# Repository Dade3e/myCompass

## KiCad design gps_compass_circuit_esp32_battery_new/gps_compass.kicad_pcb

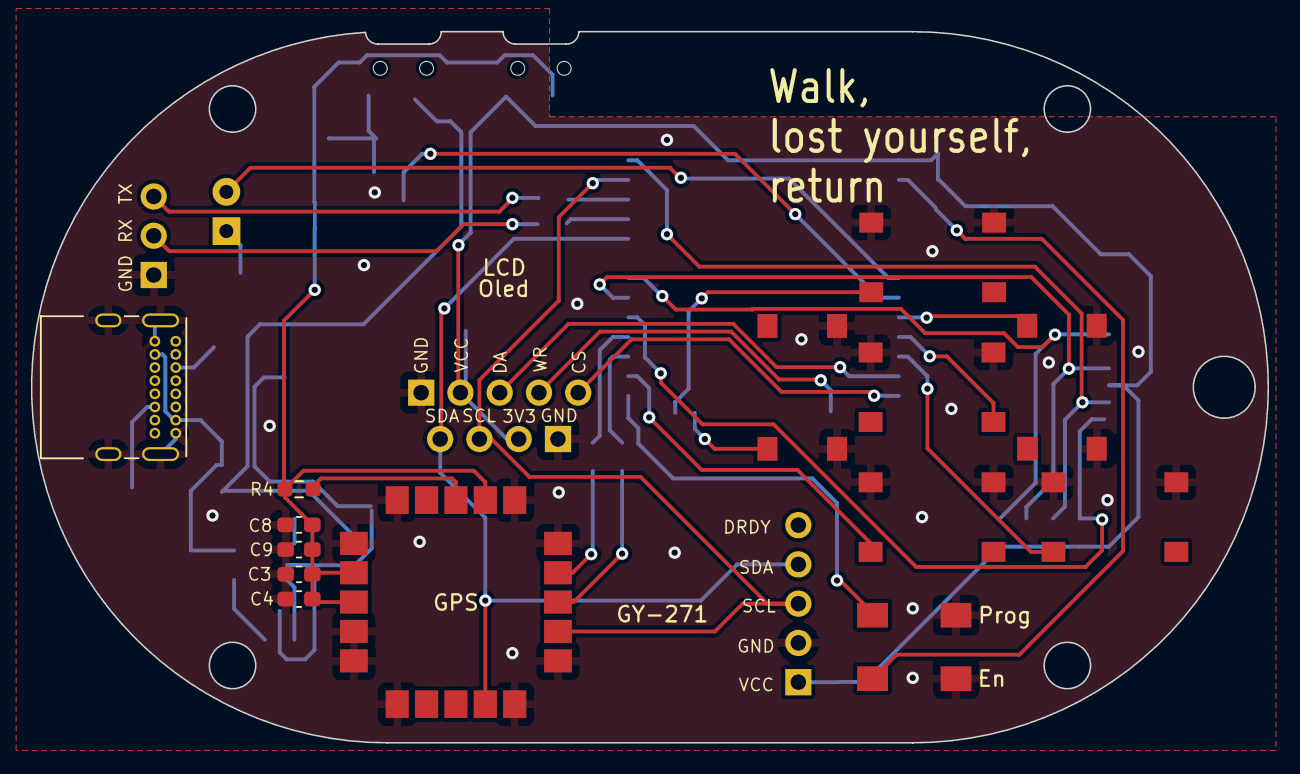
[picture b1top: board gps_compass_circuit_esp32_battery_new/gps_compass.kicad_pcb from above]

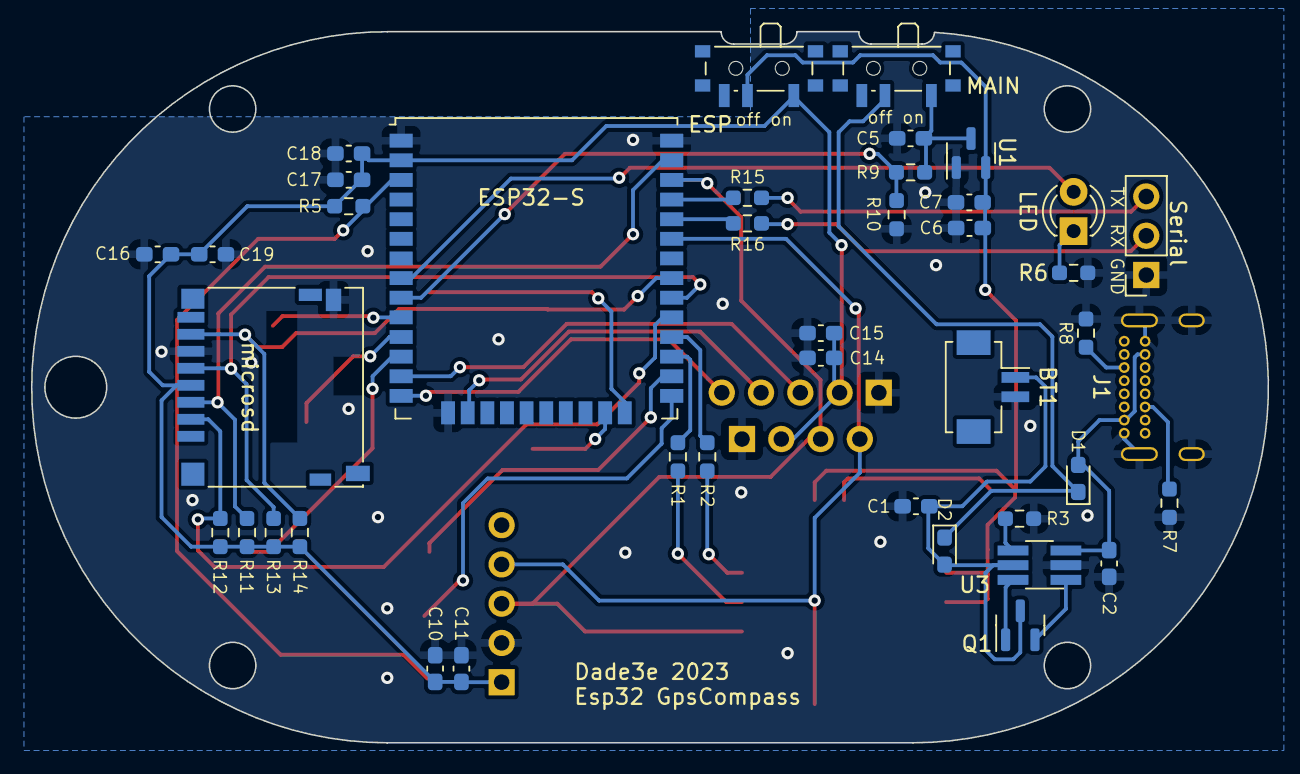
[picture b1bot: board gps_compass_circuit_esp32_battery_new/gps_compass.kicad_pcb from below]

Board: 2 copper layers, 80.0 x 46.0 mm, 58 parts (40 on the bottom side), 41 nets.

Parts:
BT1: Battery_Cell; Hirose_DF13C_CL535-0402-2-51_1x02-1MP_P1.25mm_Vertical
C1: 10uF; C_0603_1608Metric_Pad1.08x0.95mm_HandSolder
C2, C5, C7, C9, C11, C15, C18, C19: 1uF; C_0603_1608Metric_Pad1.08x0.95mm_HandSolder
C3, C4, C6, C8, C10, C14, C16, C17: 0,1uF; C_0603_1608Metric_Pad1.08x0.95mm_HandSolder
D1, D2: D; D_0603_1608Metric_Pad1.05x0.95mm_HandSolder
ESP: SW_SPDT; SW_SPDT_PCM12
ESP32-S: ESP32-WROOM-32U
En: SW_SPST; SW_SPST_EVQPE1
GPS: SAM-M8Q; ublox_SAM-M8Q
GY-271: Conn_01x05_Socket; GY-271
J1: USB_C_Receptacle_PowerOnly_6P; USB_C_Receptacle_GCT_USB4085
LCD: Conn_01x05_Socket; display_7_segm_4_digits
LED: LED; LED_D3.0mm
MAIN: SW_SPDT; SW_SPDT_PCM12
Oled: Conn_01x04_Socket; Display_i2c_128x64
Prog: SW_SPST; SW_SPST_EVQPE1
Q1: MMBTA92; SOT-23
R1, R2, R15, R16: 100R; R_0603_1608Metric_Pad0.98x0.95mm_HandSolder
R3: 5K; R_0603_1608Metric_Pad0.98x0.95mm_HandSolder
R4: 3,3K; R_0603_1608Metric_Pad0.98x0.95mm_HandSolder
R5, R11: 10K; R_0603_1608Metric_Pad0.98x0.95mm_HandSolder
R6: R; R_0603_1608Metric_Pad0.98x0.95mm_HandSolder
R7, R8: 5K1; R_0603_1608Metric_Pad0.98x0.95mm_HandSolder
R9: 27K; R_0603_1608Metric_Pad0.98x0.95mm_HandSolder
R10: 100K; R_0603_1608Metric_Pad0.98x0.95mm_HandSolder
R12, R13, R14: 47K; R_0603_1608Metric_Pad0.98x0.95mm_HandSolder
SWa1: SW_SPST; SW_Push_1P1T_NO_6x6mm_H9.5mm
SWb1: SW_SPST; SW_Push_1P1T_NO_6x6mm_H9.5mm
SWdown1: SW_SPST; SW_Push_1P1T_NO_6x6mm_H9.5mm
SWleft1: SW_SPST; SW_Push_1P1T_NO_6x6mm_H9.5mm
SWright1: SW_SPST; SW_Push_1P1T_NO_6x6mm_H9.5mm
SWup1: SW_SPST; SW_Push_1P1T_NO_6x6mm_H9.5mm
Serial: Conn_01x03_Socket; PinSocket_1x03_P2.54mm_Vertical
U1: MCP1700x-330xxTT; SOT-23
U3: LTC4054ES5-4.2; TSOT-23-6_HandSoldering
microsd: Micro_SD_Card; microSD_HC_Hirose_DM3D-SF

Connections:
+3V3: C3.1, C4.1, C6.1, C7.1, C8.1, C9.1, ESP.2 (B), GPS.2 (VCC_IO), GPS.3 (V_BCKP), GPS.17 (VCC), R4.2, U1.2 (VO)
+BATT: C5.1, MAIN.1 (A), R9.1, U1.3 (VI)
B1: ESP32-S.24 (IO2), SWup1.1 (A)
B2: ESP32-S.26 (IO4), SWdown1.1 (A)
B3: ESP32-S.23 (IO15), SWleft1.1 (A)
B4: ESP32-S.10 (IO25), SWright1.1 (A)
B5: ESP32-S.11 (IO26), SWa1.1 (A)
B6: ESP32-S.12 (IO27), SWb1.1 (A)
CLK: ESP32-S.30 (IO18), R13.2, microsd.5 (CLK)
CS: ESP32-S.29 (IO5), R12.2, microsd.2 (DAT3/CD)
GND: BT1.2 (-), C1.2, C2.2, C3.2, C4.2, C5.2, C6.2, C7.2, C8.2, C9.2, C10.1, C11.1, C14.1, C15.1, C16.2, C17.2, C18.2, C19.2, ESP32-S.1 (GND), ESP32-S.15 (GND), ESP32-S.38 (GND), En.1 (A), GPS.1 (GND), GPS.4 (GND), GPS.5 (GND), GPS.6 (GND), GPS.10 (GND), GPS.11 (GND), GPS.15 (GND), GPS.16 (GND), GPS.20 (GND), GY-271.2, J1.A12 (GND), J1.B12 (GND), J1.S1 (SHIELD), LCD.1, Oled.1, Prog.2 (B), R3.2, R6.2, R7.2, R8.2, R10.2, SWa1.2 (B), SWb1.2 (B), SWdown1.2 (B), SWleft1.2 (B), SWright1.2 (B), SWup1.2 (B), Serial.1, U1.1 (GND), U3.2 (GND), microsd.6 (VSS), microsd.9 (SHIELD)
MISO: ESP32-S.31 (IO19), R14.2, microsd.7 (DAT0)
MOSI: ESP32-S.37 (IO23), R11.2, microsd.3 (CMD)
unnamed: BT1.1 (+), C1.1, D2.2 (A), Q1.3 (C), U3.5 (BATT)
unnamed: C2.1, D1.2 (A), J1.A9 (VBUS), J1.B9 (VBUS), U3.3 (VCC)
unnamed: D1.1 (K), D2.1 (K), MAIN.2 (B)
unnamed: ESP32-S.8 (IO32), LED.2 (A)
unnamed: LED.1 (K), R6.1
unnamed: ESP32-S.3 (EN), En.2 (B), R5.2
unnamed: ESP32-S.25 (IO0), Prog.1 (A)
unnamed: ESP32-S.34 (RXD0/IO3), R16.1
unnamed: ESP32-S.35 (TXD0/IO1), R15.1
unnamed: GPS.14 (RXD), R2.2
unnamed: GPS.13 (TXD), R1.2
unnamed: GPS.18 (~RESET), R4.1
unnamed: J1.A5 (CC1), R8.1
unnamed: J1.B5 (CC2), R7.1
unnamed: Q1.1 (B), U3.6 (DRIVE)
unnamed: Q1.2 (E), U3.1 (Isense)
unnamed: R16.2, Serial.2
unnamed: R15.2, Serial.3
unnamed: R3.1, U3.4 (Prog)
RX2: ESP32-S.27 (IO16), R1.1
SCL: ESP32-S.36 (IO22), GPS.12 (SCL), GY-271.3, Oled.3
SDA: ESP32-S.33 (IO21), GPS.9 (SDA), GY-271.4, Oled.4
TX2: ESP32-S.28 (IO17), R2.1
VCC: C10.2, C11.2, C14.2, C15.2, C16.1, C17.1, C18.1, C19.1, ESP.1 (A), ESP32-S.2 (VDD), GY-271.1, LCD.2, Oled.2, R5.1, R11.1, R12.1, R13.1, R14.1, microsd.4 (VDD)
battery_level: ESP32-S.9 (IO33), R9.2, R10.1
lcd_cs: ESP32-S.14 (IO12), LCD.5
lcd_data: ESP32-S.13 (IO14), LCD.3
lcd_wr: ESP32-S.16 (IO13), LCD.4

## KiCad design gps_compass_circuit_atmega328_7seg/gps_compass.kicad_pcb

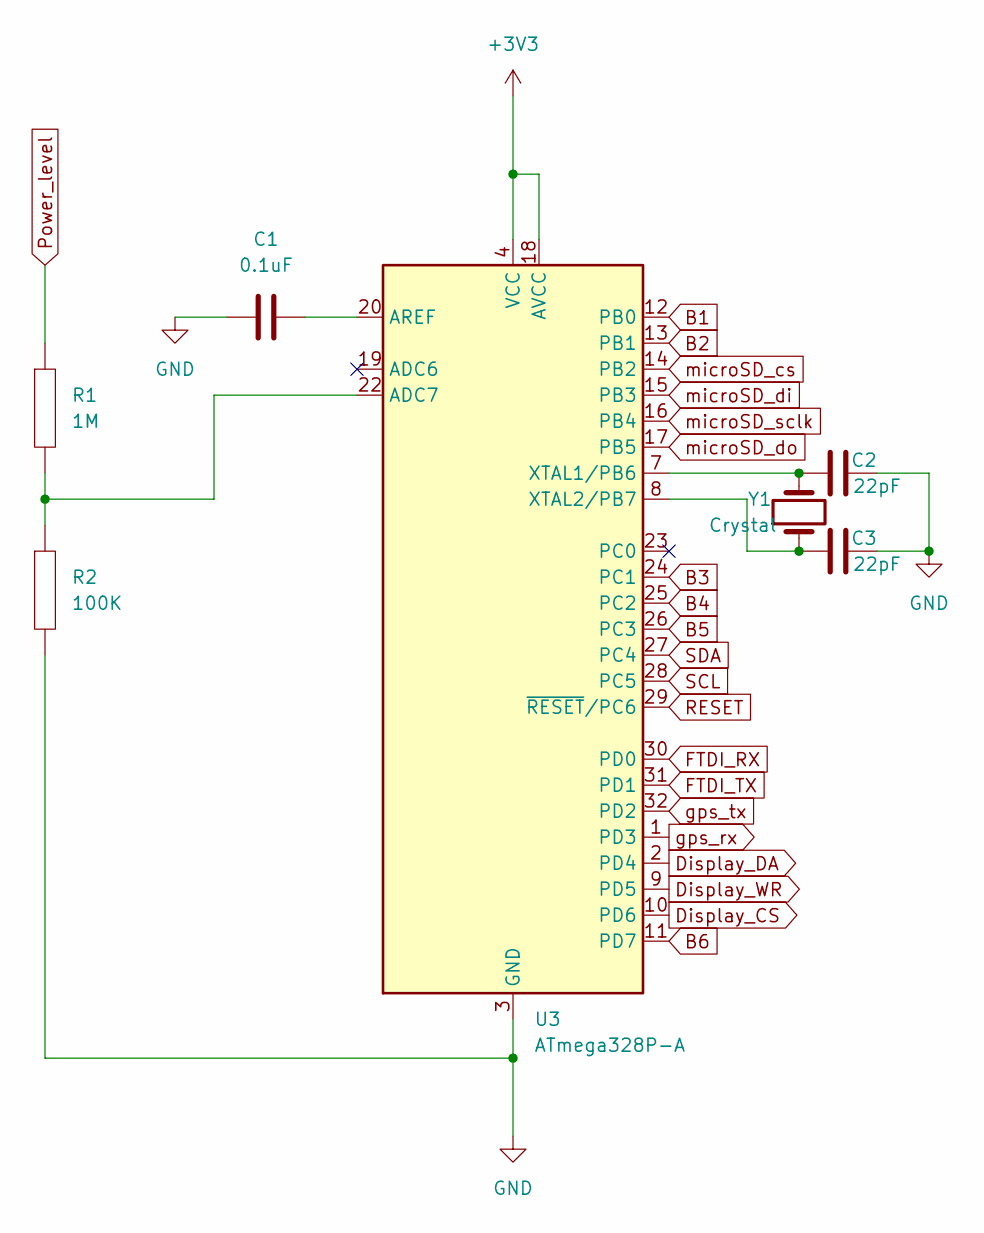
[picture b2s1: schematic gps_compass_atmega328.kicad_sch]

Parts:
C1: 0.1uF; C_0603_1608Metric
C2, C3: 22pF; C_0603_1608Metric
R1: 1M; C_0603_1608Metric
R2: 100K; C_0603_1608Metric
U3: ATmega328P-A; TQFP-32_7x7mm_P0.8mm
Y1: Crystal; Resonator-2Pin_W10.0mm_H5.0mm

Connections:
+3V3: U3.4 (VCC), U3.6 (VCC), U3.18 (AVCC); also elsewhere on the board
B1: U3.12 (PB0); also elsewhere on the board
B2: U3.13 (PB1); also elsewhere on the board
B3: U3.24 (PC1); also elsewhere on the board
B4: U3.25 (PC2); also elsewhere on the board
B5: U3.26 (PC3); also elsewhere on the board
B6: U3.11 (PD7); also elsewhere on the board
Display_CS: U3.10 (PD6); also elsewhere on the board
Display_DA: U3.2 (PD4); also elsewhere on the board
Display_WR: U3.9 (PD5); also elsewhere on the board
FTDI_RX: U3.30 (PD0); also elsewhere on the board
FTDI_TX: U3.31 (PD1); also elsewhere on the board
GND: C1.1, C2.2, C3.2, R2.2, U3.3 (GND), U3.5 (GND), U3.21 (GND); also elsewhere on the board
unnamed: R1.2, R2.1, U3.22 (ADC7)
unnamed: C1.2, U3.20 (AREF)
unnamed: C2.1, U3.7 (XTAL1/PB6), Y1.2
unnamed: C3.1, U3.8 (XTAL2/PB7), Y1.1
Power_level: R1.1; also elsewhere on the board
RESET: U3.29 (~RESET/PC6); also elsewhere on the board
SCL: U3.28 (PC5); also elsewhere on the board
SDA: U3.27 (PC4); also elsewhere on the board
gps_rx: U3.1 (PD3); also elsewhere on the board
gps_tx: U3.32 (PD2); also elsewhere on the board
microSD_cs: U3.14 (PB2); also elsewhere on the board
microSD_di: U3.15 (PB3); also elsewhere on the board
microSD_do: U3.17 (PB5); also elsewhere on the board
microSD_sclk: U3.16 (PB4); also elsewhere on the board

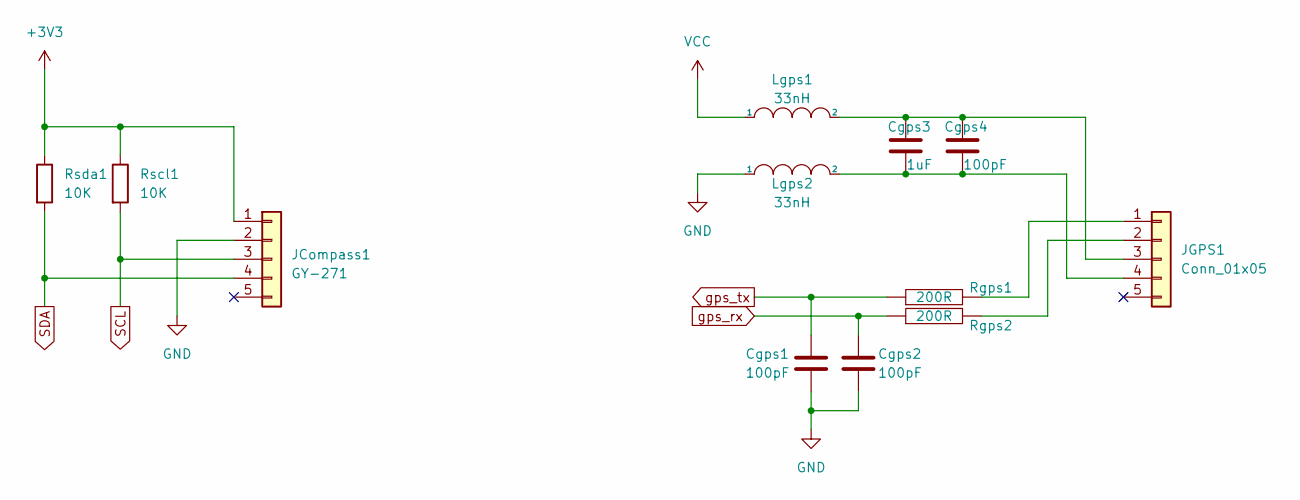
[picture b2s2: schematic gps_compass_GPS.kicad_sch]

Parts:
Cgps1, Cgps2, Cgps4: 100pF; C_0603_1608Metric
Cgps3: 1uF; C_0603_1608Metric
JCompass1: GY-271
JGPS1: Conn_01x05; PinSocket_1x05_P2.54mm_Vertical
Lgps1, Lgps2: 33nH; L_0603_1608Metric
Rgps1, Rgps2: 200R; R_0603_1608Metric
Rscl1: 10K; R_0603_1608Metric
Rsda1: 10K; R_0603_1608Metric

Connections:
+3V3: JCompass1.1, Rscl1.1, Rsda1.1; also elsewhere on the board
GND: Cgps1.2, Cgps2.2, JCompass1.2, Lgps2.1; also elsewhere on the board
unnamed: JGPS1.1, Rgps1.2
unnamed: JGPS1.2, Rgps2.2
unnamed: Cgps3.1, Cgps4.1, JGPS1.3, Lgps1.2
unnamed: Cgps3.2, Cgps4.2, JGPS1.4, Lgps2.2
SCL: JCompass1.3, Rscl1.2; also elsewhere on the board
SDA: JCompass1.4, Rsda1.2; also elsewhere on the board
VCC: Lgps1.1; also elsewhere on the board
gps_rx: Cgps2.1, Rgps2.1; also elsewhere on the board
gps_tx: Cgps1.1, Rgps1.1; also elsewhere on the board

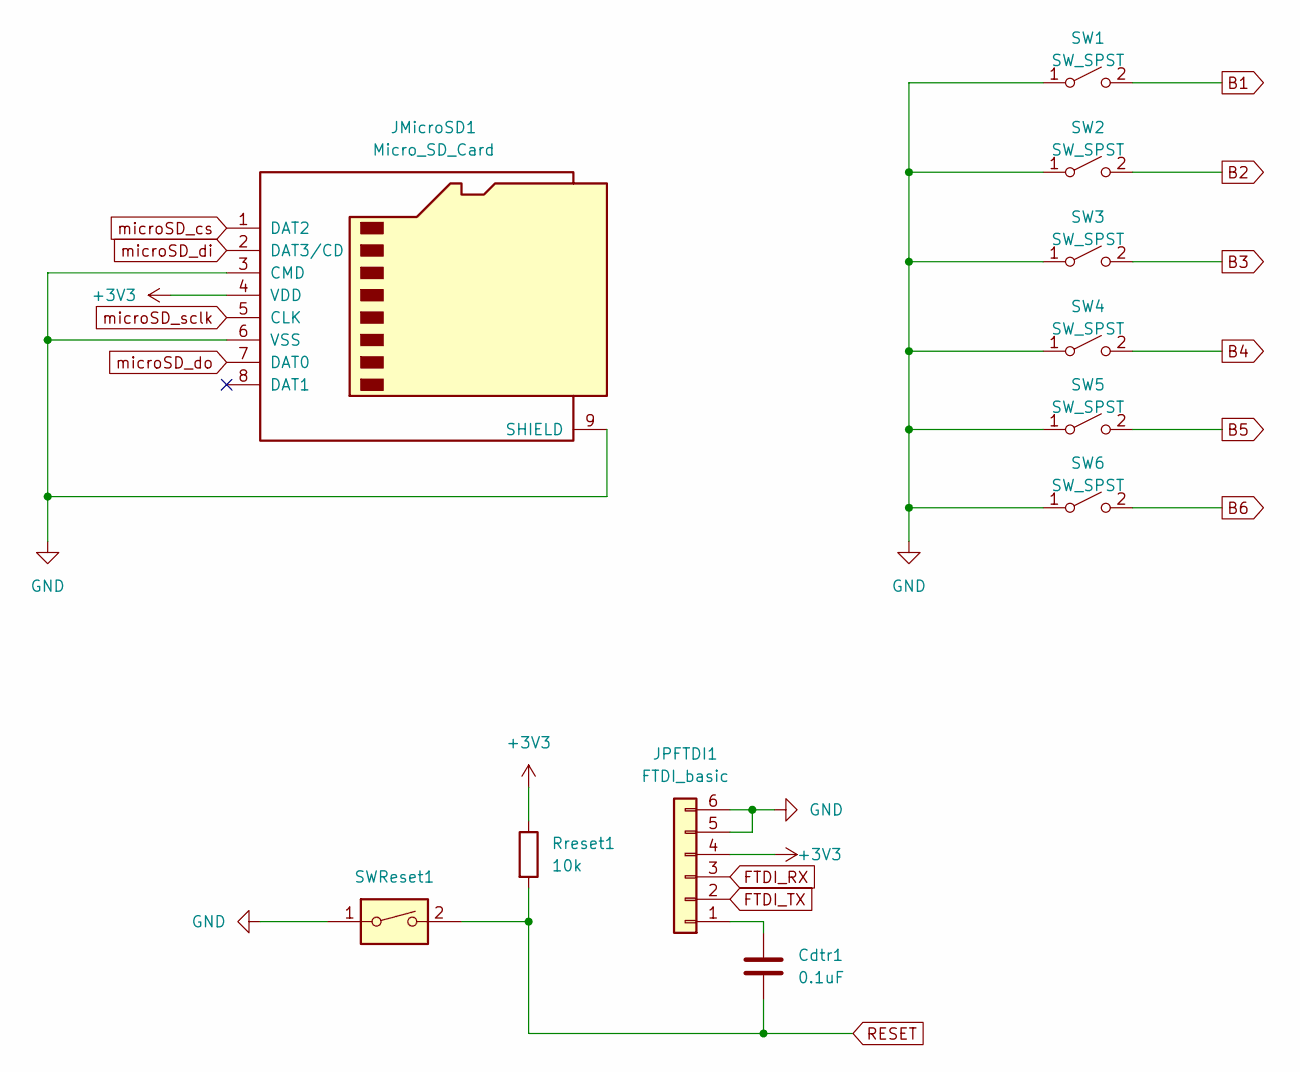
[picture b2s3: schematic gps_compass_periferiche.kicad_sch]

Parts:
Cdtr1: 0.1uF; R_0603_1608Metric
JMicroSD1: Micro_SD_Card; microSD_HC_Molex_47219-2001
JPFTDI1: FTDI_basic; PinSocket_1x06_P2.54mm_Horizontal
Rreset1: 10k; R_0603_1608Metric
SW1, SW2, SW3, SW4, SW5, SW6: SW_SPST; SW_PUSH_6mm
SWReset1: SW_Reset; SW_PUSH_6mm

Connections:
+3V3: JMicroSD1.4 (VDD), JPFTDI1.4, Rreset1.1; also elsewhere on the board
B1: SW1.2 (B); also elsewhere on the board
B2: SW2.2 (B); also elsewhere on the board
B3: SW3.2 (B); also elsewhere on the board
B4: SW4.2 (B); also elsewhere on the board
B5: SW5.2 (B); also elsewhere on the board
B6: SW6.2 (B); also elsewhere on the board
FTDI_RX: JPFTDI1.3; also elsewhere on the board
FTDI_TX: JPFTDI1.2; also elsewhere on the board
GND: JMicroSD1.3 (CMD), JMicroSD1.6 (VSS), JMicroSD1.9 (SHIELD), JPFTDI1.5, JPFTDI1.6, SW1.1 (A), SW2.1 (A), SW3.1 (A), SW4.1 (A), SW5.1 (A), SW6.1 (A), SWReset1.1; also elsewhere on the board
unnamed: Cdtr1.2, JPFTDI1.1
RESET: Cdtr1.1, Rreset1.2, SWReset1.2; also elsewhere on the board
microSD_cs: JMicroSD1.1 (DAT2); also elsewhere on the board
microSD_di: JMicroSD1.2 (DAT3/CD); also elsewhere on the board
microSD_do: JMicroSD1.7 (DAT0); also elsewhere on the board
microSD_sclk: JMicroSD1.5 (CLK); also elsewhere on the board

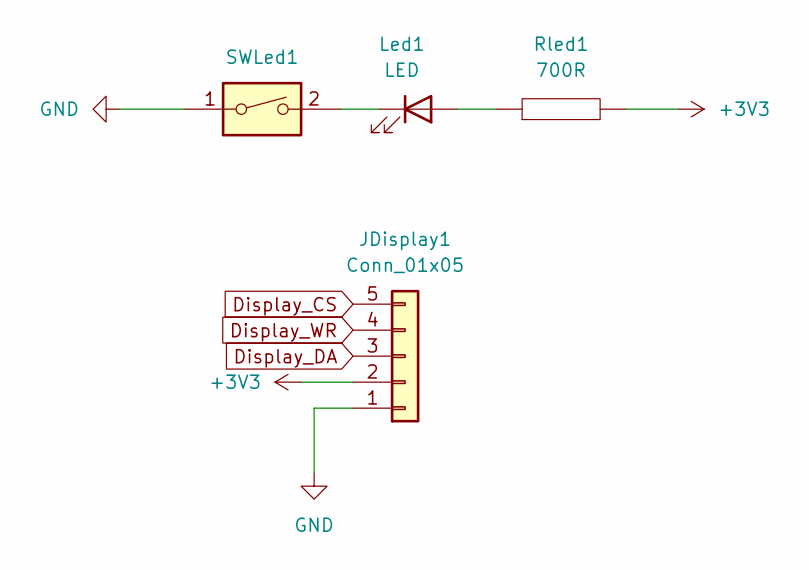
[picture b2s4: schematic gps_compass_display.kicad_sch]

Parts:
JDisplay1: Conn_01x05; display_7_segm_4_digits
Led1: LED; LED_D3.0mm
Rled1: 700R; R_0603_1608Metric
SWLed1: SW_Reset; SW_PUSH_6mm

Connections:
+3V3: JDisplay1.2, Rled1.2; also elsewhere on the board
Display_CS: JDisplay1.5; also elsewhere on the board
Display_DA: JDisplay1.3; also elsewhere on the board
Display_WR: JDisplay1.4; also elsewhere on the board
GND: JDisplay1.1, SWLed1.1; also elsewhere on the board
unnamed: Led1.2 (A), Rled1.1
unnamed: Led1.1 (K), SWLed1.2

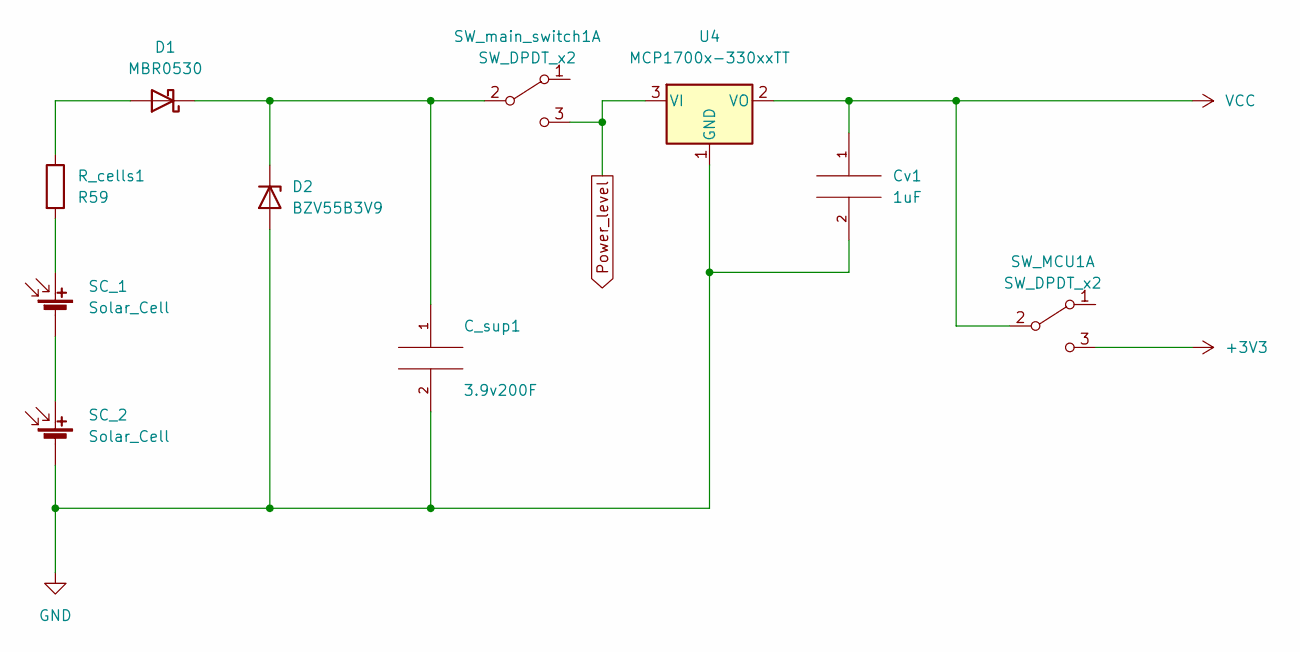
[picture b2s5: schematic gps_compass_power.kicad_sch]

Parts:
C_sup1: 3.9v200F; C_Rect_L9.0mm_W2.5mm_P7.50mm_MKT
Cv1: 1uF; C_0603_1608Metric
D1: MBR0530; D_SOD-123
D2: BZV55B3V9; D_A-405_P7.62mm_Horizontal
R_cells1: R59; R_0603_1608Metric
SC_1, SC_2: Solar_Cell; solar_panel
SW_MCU1: SW_DPDT_x2; PinSocket_1x03_P2.54mm_Vertical
SW_main_switch1: SW_DPDT_x2; PinSocket_1x03_P2.54mm_Vertical
U4: MCP1700x-330xxTT; SOT-23

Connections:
+3V3: SW_MCU1.3 (C); also elsewhere on the board
GND: C_sup1.2, Cv1.2, D2.2 (A), SC_2.2 (-), U4.1 (GND); also elsewhere on the board
unnamed: D1.2 (A), R_cells1.1
unnamed: C_sup1.1, D1.1 (K), D2.1 (K), SW_main_switch1.2 (B)
unnamed: R_cells1.2, SC_1.1 (+)
unnamed: SC_1.2 (-), SC_2.1 (+)
Power_level: SW_main_switch1.3 (C), U4.3 (VI); also elsewhere on the board
VCC: Cv1.1, SW_MCU1.2 (B), U4.2 (VO); also elsewhere on the board

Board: 2 copper layers, 44 parts (0 on the bottom side), 39 nets, no tracks yet.

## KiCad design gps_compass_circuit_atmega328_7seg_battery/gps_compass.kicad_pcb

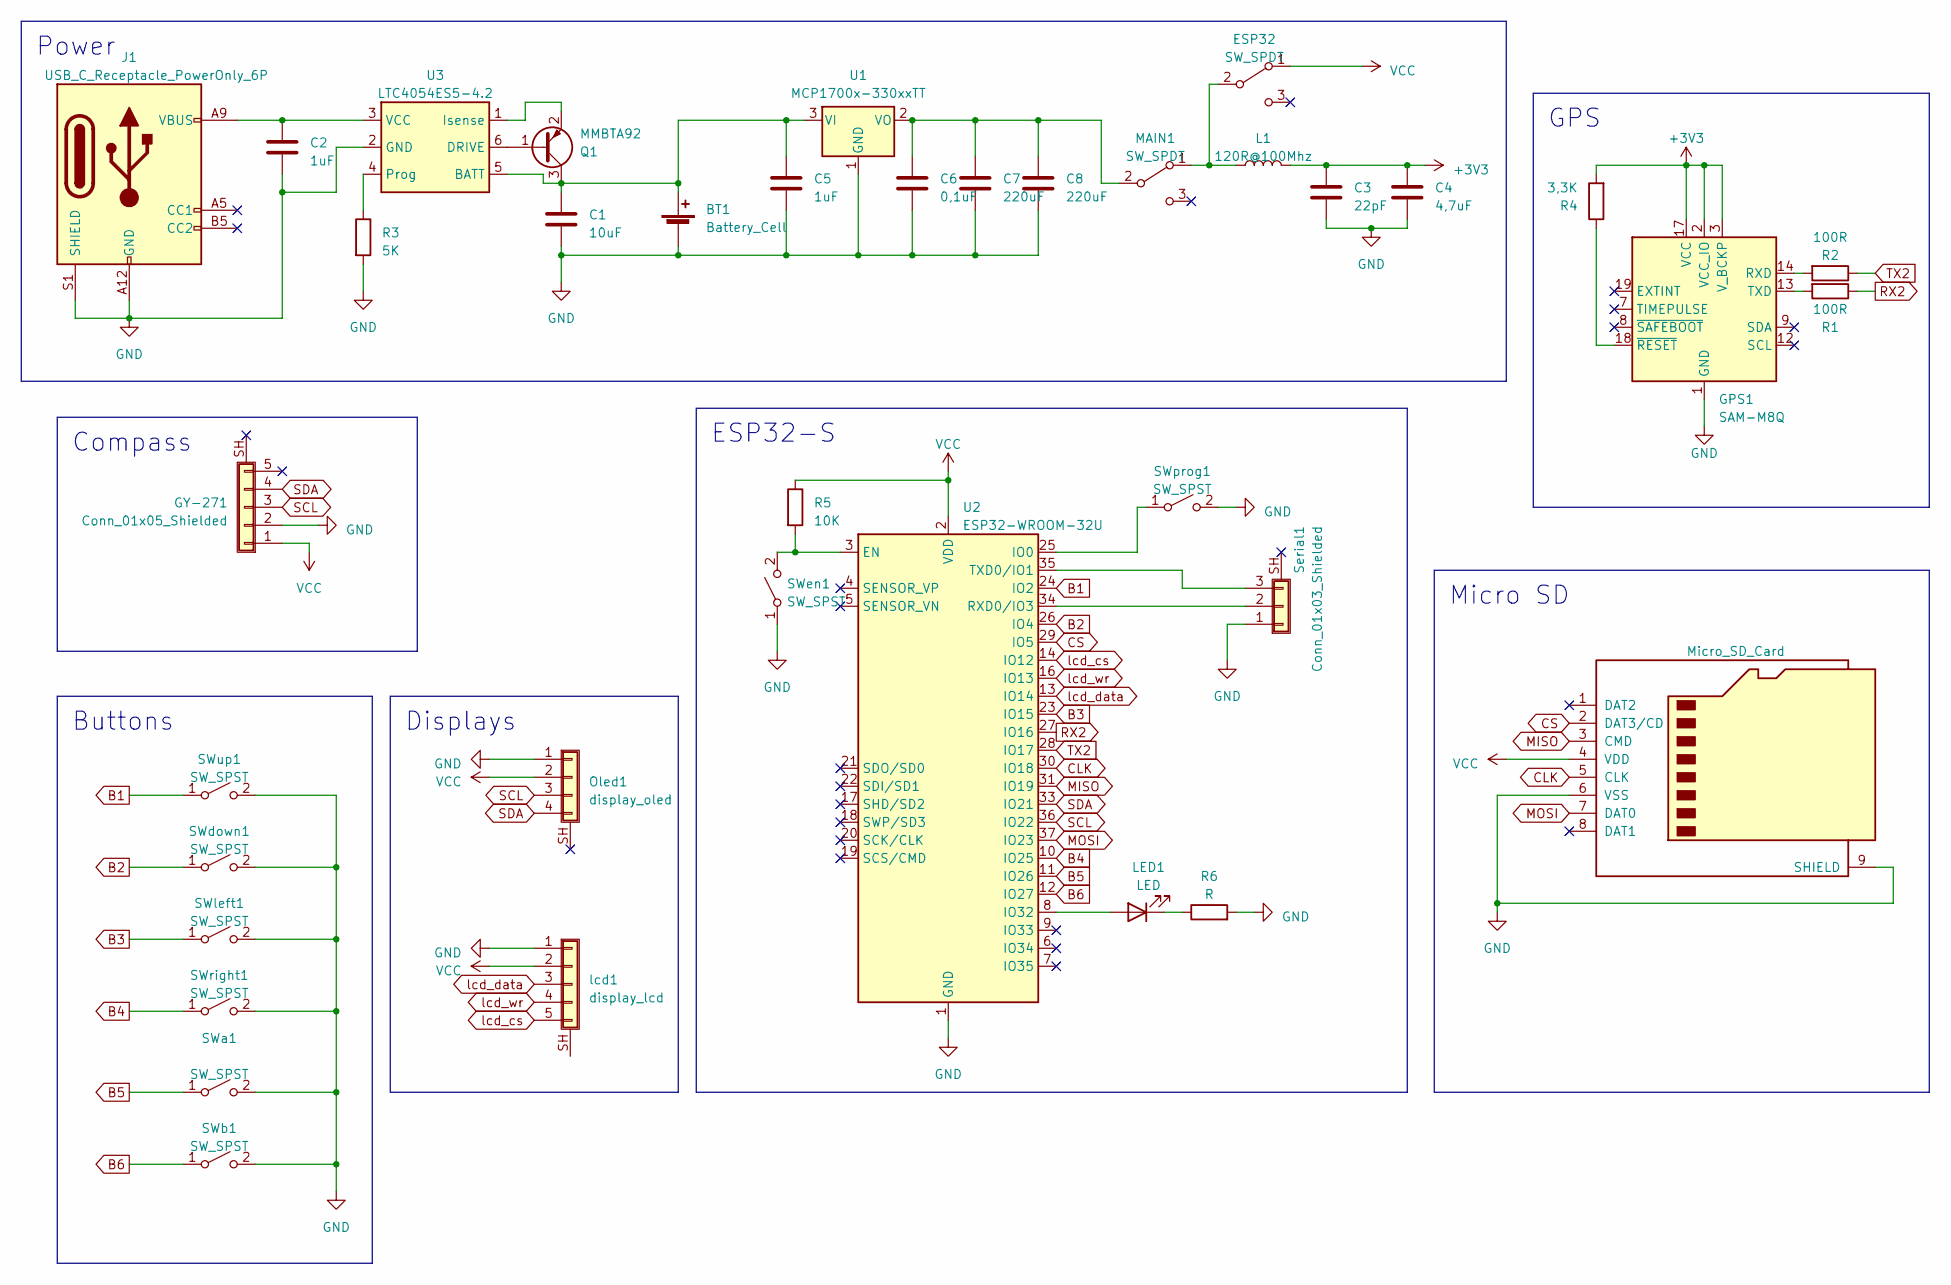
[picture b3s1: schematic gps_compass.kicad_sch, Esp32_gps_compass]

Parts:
BT1: Battery_Cell; Hirose_DF13C_CL535-0402-2-51_1x02-1MP_P1.25mm_Vertical
C1: 10uF; C_0805_2012Metric_Pad1.18x1.45mm_HandSolder
C2, C5: 1uF; C_0805_2012Metric_Pad1.18x1.45mm_HandSolder
C3: 22pF; C_0805_2012Metric_Pad1.18x1.45mm_HandSolder
C4: 4,7uF; C_0805_2012Metric_Pad1.18x1.45mm_HandSolder
C6: 0,1uF; C_0805_2012Metric_Pad1.18x1.45mm_HandSolder
C7, C8: 220uF; C_1206_3216Metric_Pad1.33x1.80mm_HandSolder
ESP32: SW_SPDT; SW_SPDT_PCM12
GPS1: SAM-M8Q; ublox_SAM-M8Q
GY-271: Conn_01x05_Shielded; GY-271
J1: USB_C_Receptacle_PowerOnly_6P; USB_C_Receptacle_GCT_USB4085
L1: 120R@100Mhz; L_0805_2012Metric_Pad1.15x1.40mm_HandSolder
LED1: LED; LED_D3.0mm
MAIN1: SW_SPDT; SW_SPDT_PCM12
Oled1: display_oled; Display_i2c_128x64
Q1: MMBTA92; SOT-23
R1, R2: 100R; R_0603_1608Metric_Pad0.98x0.95mm_HandSolder
R3: 5K; R_0603_1608Metric_Pad0.98x0.95mm_HandSolder
R4: 3,3K; R_0603_1608Metric_Pad0.98x0.95mm_HandSolder
R5: 10K; R_0603_1608Metric_Pad0.98x0.95mm_HandSolder
R6: R; R_0603_1608Metric_Pad0.98x0.95mm_HandSolder
SWa1: SW_SPST; SW_PUSH_6mm
SWb1: SW_SPST; SW_PUSH_6mm
SWdown1: SW_SPST; SW_PUSH_6mm
SWen1: SW_SPST; SW_SPST_EVQPE1
SWleft1: SW_SPST; SW_PUSH_6mm
SWprog1: SW_SPST; SW_SPST_EVQPE1
SWright1: SW_SPST; SW_PUSH_6mm
SWup1: SW_SPST; SW_PUSH_6mm
Serial1: Conn_01x03_Shielded; PinSocket_1x03_P2.54mm_Vertical
U1: MCP1700x-330xxTT; SOT-23
U2: ESP32-WROOM-32U
U3: LTC4054ES5-4.2; TSOT-23-6_HandSoldering
lcd1: display_lcd; display_7_segm_4_digits
microsd1: Micro_SD_Card; microSD_HC_Hirose_DM3D-SF

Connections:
+3V3: C3.1, C4.1, GPS1.2 (VCC_IO), GPS1.3 (V_BCKP), GPS1.17 (VCC), L1.2, R4.2
B1: SWup1.1 (A), U2.24 (IO2)
B2: SWdown1.1 (A), U2.26 (IO4)
B3: SWleft1.1 (A), U2.23 (IO15)
B4: SWright1.1 (A), U2.10 (IO25)
B5: SWa1.1 (A), U2.11 (IO26)
B6: SWb1.1 (A), U2.12 (IO27)
CLK: U2.30 (IO18), microsd1.5 (CLK)
CS: U2.29 (IO5), microsd1.2 (DAT3/CD)
GND: BT1.2 (-), C1.2, C2.2, C3.2, C4.2, C5.2, C6.2, C7.2, C8.2, GPS1.1 (GND), GPS1.4 (GND), GPS1.5 (GND), GPS1.6 (GND), GPS1.10 (GND), GPS1.11 (GND), GPS1.15 (GND), GPS1.16 (GND), GPS1.20 (GND), GY-271.2, J1.A12 (GND), J1.B12 (GND), J1.S1 (SHIELD), Oled1.1, R3.2, R6.2, SWa1.2 (B), SWb1.2 (B), SWdown1.2 (B), SWen1.1 (A), SWleft1.2 (B), SWprog1.2 (B), SWright1.2 (B), SWup1.2 (B), Serial1.1, U1.1 (GND), U2.1 (GND), U2.15 (GND), U2.38 (GND), U2.39 (GND), U3.2 (GND), lcd1.1, microsd1.6 (VSS), microsd1.9 (SHIELD)
MISO: U2.31 (IO19), microsd1.3 (CMD)
MOSI: U2.37 (IO23), microsd1.7 (DAT0)
unnamed: BT1.1 (+), C1.1, C5.1, Q1.3 (C), U1.3 (VI), U3.5 (BATT)
unnamed: ESP32.2 (B), L1.1, MAIN1.1 (A)
unnamed: GPS1.14 (RXD), R2.2
unnamed: GPS1.13 (TXD), R1.2
unnamed: GPS1.18 (~RESET), R4.1
unnamed: LED1.2 (A), U2.8 (IO32)
unnamed: LED1.1 (K), R6.1
unnamed: C6.1, C7.1, C8.1, MAIN1.2 (B), U1.2 (VO)
unnamed: Q1.1 (B), U3.6 (DRIVE)
unnamed: Q1.2 (E), U3.1 (Isense)
unnamed: R5.2, SWen1.2 (B), U2.3 (EN)
unnamed: SWprog1.1 (A), U2.25 (IO0)
unnamed: Serial1.2, U2.34 (RXD0/IO3)
unnamed: Serial1.3, U2.35 (TXD0/IO1)
unnamed: R3.1, U3.4 (Prog)
unnamed: C2.1, J1.A9 (VBUS), J1.B9 (VBUS), U3.3 (VCC)
RX2: R1.1, U2.27 (IO16)
SCL: GY-271.3, Oled1.3, U2.36 (IO22)
SDA: GY-271.4, Oled1.4, U2.33 (IO21)
TX2: R2.1, U2.28 (IO17)
VCC: ESP32.1 (A), GY-271.1, Oled1.2, R5.1, U2.2 (VDD), lcd1.2, microsd1.4 (VDD)
lcd_cs: U2.14 (IO12), lcd1.5
lcd_data: U2.13 (IO14), lcd1.3
lcd_wr: U2.16 (IO13), lcd1.4

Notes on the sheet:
Displays
ESP32-S
Buttons
Micro SD
Compass
Power
GPS

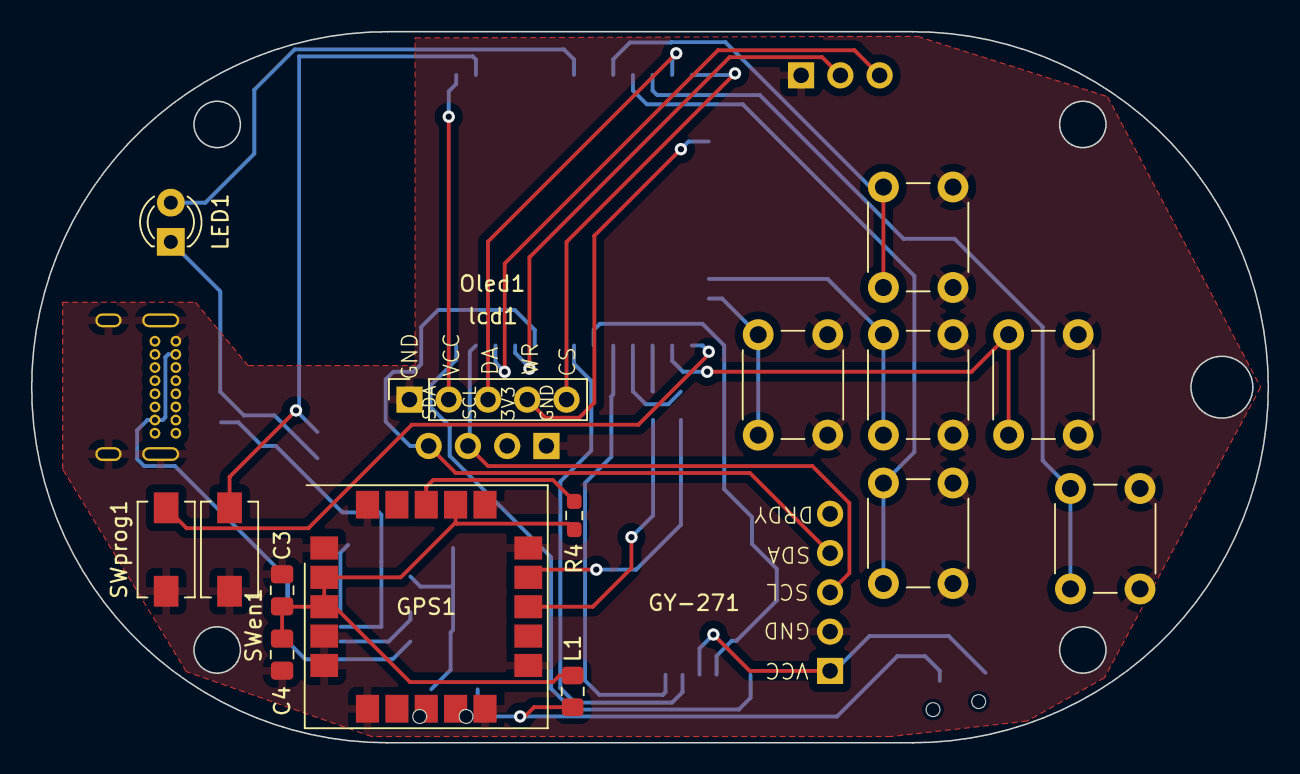
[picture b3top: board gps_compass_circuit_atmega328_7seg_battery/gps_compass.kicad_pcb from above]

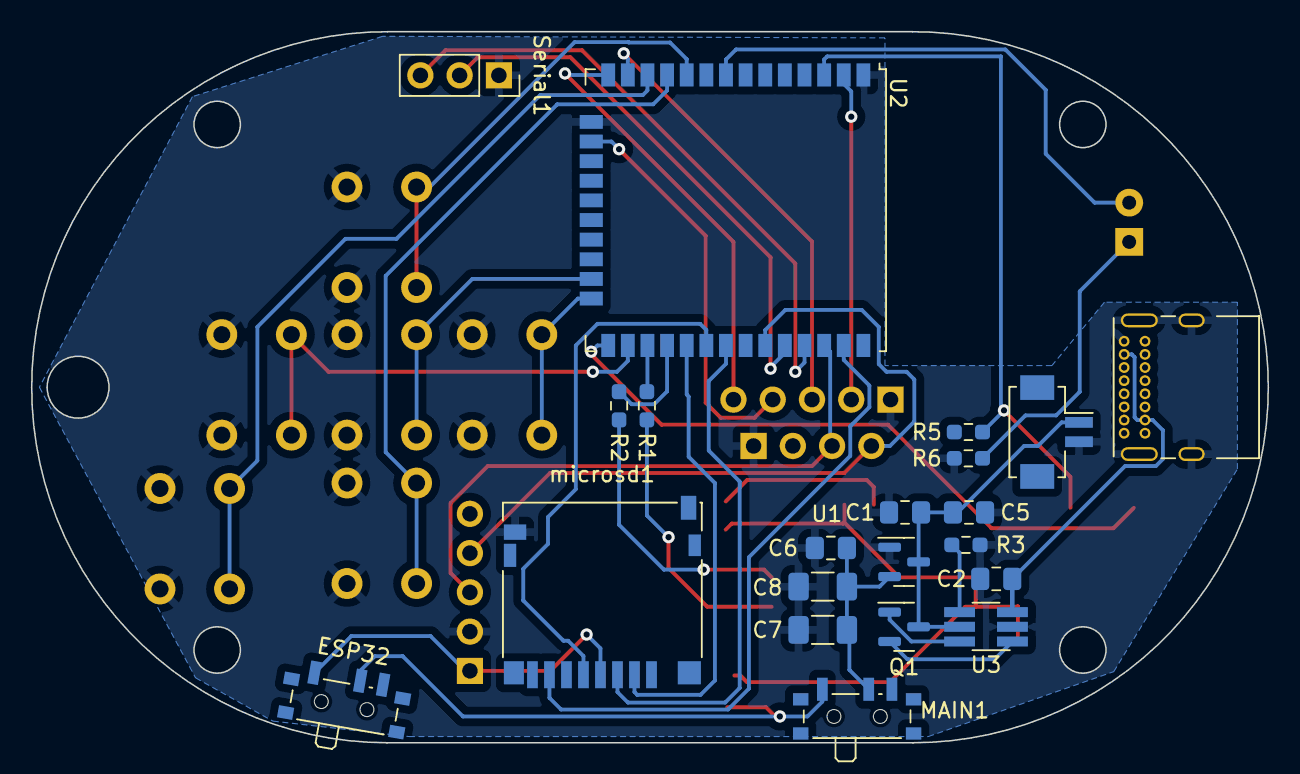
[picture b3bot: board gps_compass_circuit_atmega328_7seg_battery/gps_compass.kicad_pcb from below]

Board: 2 copper layers, 80.0 x 46.0 mm, 38 parts (21 on the bottom side), 36 nets.

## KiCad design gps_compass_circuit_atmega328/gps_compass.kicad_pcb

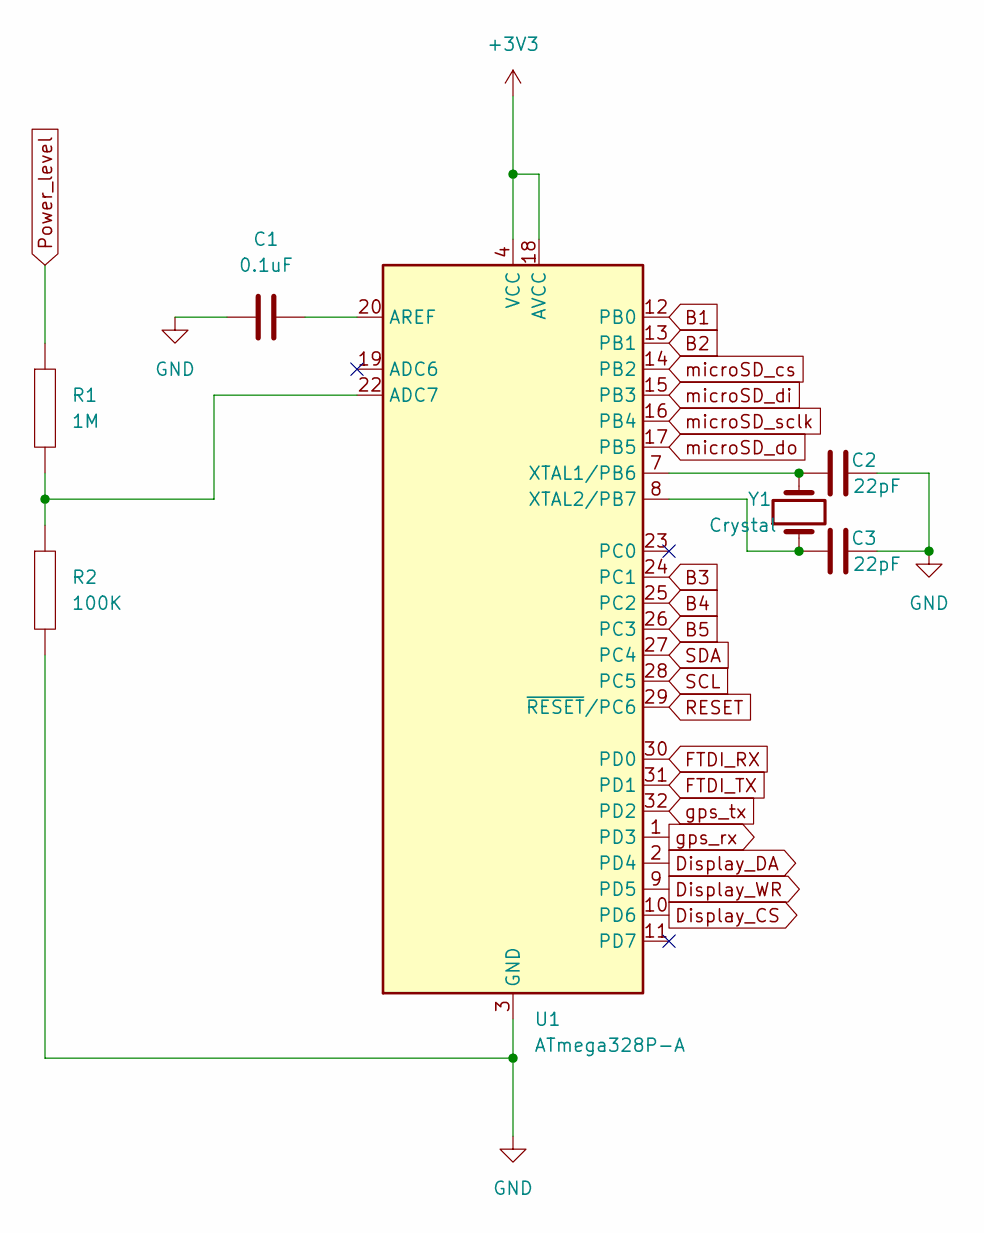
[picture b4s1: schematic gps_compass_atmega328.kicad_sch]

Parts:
C1: 0.1uF; C_0603_1608Metric
C2, C3: 22pF; C_0603_1608Metric
R1: 1M; C_0603_1608Metric
R2: 100K; C_0603_1608Metric
U1: ATmega328P-A; TQFP-32_7x7mm_P0.8mm
Y1: Crystal; Resonator-2Pin_W10.0mm_H5.0mm

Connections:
+3V3: U1.4 (VCC), U1.6 (VCC), U1.18 (AVCC); also elsewhere on the board
B1: U1.12 (PB0); also elsewhere on the board
B2: U1.13 (PB1); also elsewhere on the board
B3: U1.24 (PC1); also elsewhere on the board
B4: U1.25 (PC2); also elsewhere on the board
B5: U1.26 (PC3); also elsewhere on the board
Display_CS: U1.10 (PD6)
Display_DA: U1.2 (PD4)
Display_WR: U1.9 (PD5)
FTDI_RX: U1.30 (PD0); also elsewhere on the board
FTDI_TX: U1.31 (PD1); also elsewhere on the board
GND: C1.1, C2.2, C3.2, R2.2, U1.3 (GND), U1.5 (GND), U1.21 (GND); also elsewhere on the board
unnamed: C1.2, U1.20 (AREF)
unnamed: C2.1, U1.7 (XTAL1/PB6), Y1.2
unnamed: C3.1, U1.8 (XTAL2/PB7), Y1.1
unnamed: R1.2, R2.1, U1.22 (ADC7)
Power_level: R1.1; also elsewhere on the board
RESET: U1.29 (~RESET/PC6); also elsewhere on the board
SCL: U1.28 (PC5); also elsewhere on the board
SDA: U1.27 (PC4); also elsewhere on the board
gps_rx: U1.1 (PD3); also elsewhere on the board
gps_tx: U1.32 (PD2); also elsewhere on the board
microSD_cs: U1.14 (PB2); also elsewhere on the board
microSD_di: U1.15 (PB3); also elsewhere on the board
microSD_do: U1.17 (PB5); also elsewhere on the board
microSD_sclk: U1.16 (PB4); also elsewhere on the board

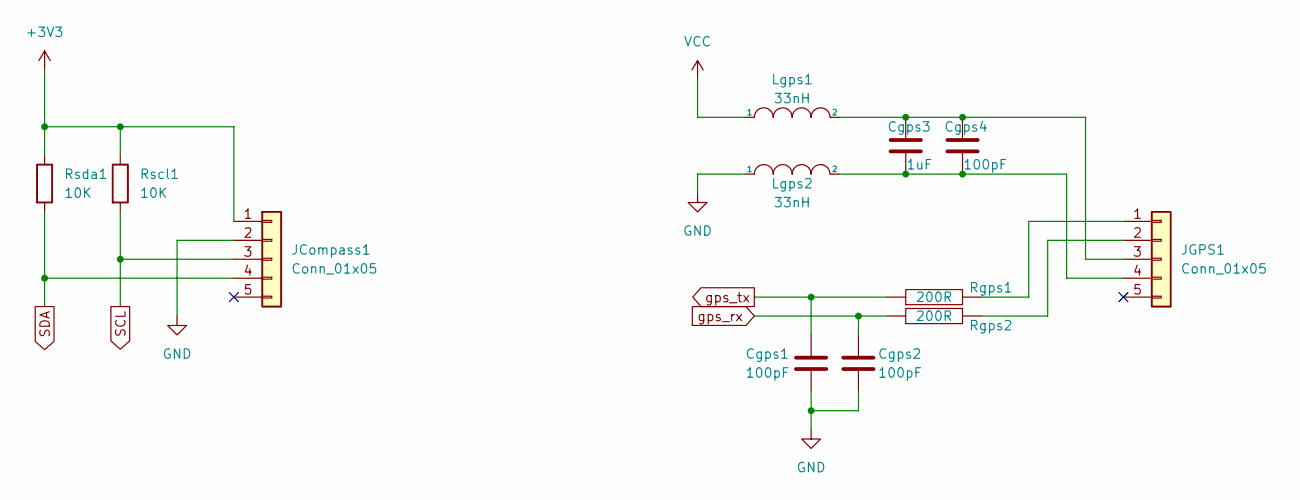
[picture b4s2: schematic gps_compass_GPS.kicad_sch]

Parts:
Cgps1, Cgps2, Cgps4: 100pF; C_0603_1608Metric
Cgps3: 1uF; C_0603_1608Metric
JCompass1: Conn_01x05; PinSocket_1x05_P2.54mm_Vertical
JGPS1: Conn_01x05; PinSocket_1x05_P2.54mm_Vertical
Lgps1, Lgps2: 33nH; L_0603_1608Metric
Rgps1, Rgps2: 200R; R_0603_1608Metric
Rscl1: 10K; R_0603_1608Metric
Rsda1: 10K; R_0603_1608Metric

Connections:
+3V3: JCompass1.1, Rscl1.1, Rsda1.1; also elsewhere on the board
GND: Cgps1.2, Cgps2.2, JCompass1.2, Lgps2.1; also elsewhere on the board
unnamed: Cgps3.1, Cgps4.1, JGPS1.3, Lgps1.2
unnamed: Cgps3.2, Cgps4.2, JGPS1.4, Lgps2.2
unnamed: JGPS1.1, Rgps1.2
unnamed: JGPS1.2, Rgps2.2
SCL: JCompass1.3, Rscl1.2; also elsewhere on the board
SDA: JCompass1.4, Rsda1.2; also elsewhere on the board
VCC: Lgps1.1; also elsewhere on the board
gps_rx: Cgps2.1, Rgps2.1; also elsewhere on the board
gps_tx: Cgps1.1, Rgps1.1; also elsewhere on the board
